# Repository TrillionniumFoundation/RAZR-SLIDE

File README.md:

# RAZR SLIDE

<!-- current-product:start -->
## Current product integration — 2026-10-23

[Current design](CURRENT_DESIGN.md) · [Machine-readable product state](design/current_product.json) · [Implementation and evidence](engineering/product-integration-20261018/README.md)

Exact functional source 042b7689 passed all 1558 actual tests in 36 locked suites, EP4/EP5 native execution and independent readers, and 36442 complete pair domains across three fixed poses. EP4 retains 55 geometric rejections. A separate accessory diagnostic cleared all 1099 continuous pair domains. Full motion remains open: KEY has preserved partial positive evidence; SLIDE native v2 was stopped by the original shared-memory guard after five factory-law probes with no recoverable completed pair rows; SEATING could not start within its original resource gates. Full original L2 K operators were faithfully rebuilt; panel response reached all 3885 columns but failed the original five-probe residual guard, and the new diagnostic could not start within its resource budget. Hosted jobs have no steps or runners. Real inputs, full motion, tolerances, structural qualification and G3-G5 hardware evidence remain unresolved.

The active milestone is a common assembly with flat OLED storage, complete terminations, A/B cell reservations and an operable manual cycle. Measured parts, source specifications and project assumptions retain separate identities.

Configured unit validation: **1564 tests / 36 suites** in `tools/test_suites.json`. Completed execution reports retain their exact commit and scope in `design/current_product.json`; a configured count is not an execution result.

Functional source 042b768903cccbd7a0995317c8598401e0318e2a: 1558 actual tests / 36 suites passed, zero failures/errors/skips, 43 locked packages and required source bytes unchanged. EP4: 15886 pair rows and 55 retained geometry rejections. EP5: 154/154/161 bodies, 36442 finite pair rows, 123 outer-union containments, independent STEP/endpoint readers passed. Three declared fixed-pose control domains: 36442 unique pairs, zero evaluation errors or collision witnesses. Original ten native jobs / 37 commands retain their e76 identity. Follow-on diagnostics record actual passes, numerical rejection, interrupted trials and refused startups separately. Hosted run 39917795794: 18 failed and one skipped job, zero steps/runners/artifacts, current cause unknown. No whole-product or physical/manufacturing acceptance follows.

Accepted numerical evidence: [PR34 installation/service](engineering/installation-control-20261018/DELIVERY_VERIFICATION.json). Bearing research and the older spring experiment retain their own versioned results in the current product state; historical failures remain preserved.
That FE evidence belongs to the original installation geometry. The newly modified product shells have not been structurally requalified.
<!-- current-product:end -->

Private engineering research repository. **`candidate_go=false`; `manufacturing_go=false`.**

## Product constraints

Equal finished A/B dimensions; one approximately 7-inch flexible OLED; no independent rear display; B travels upward 79.75 mm, then seats normally by 8.20 mm; A has priority for the larger battery. 4700 mAh is the unverified TOTAL SYSTEM target; individual A/B cells and capacities are unselected.

## Historical repair baseline

**R50_20261011 is the integration and rejection-validation base**, original archive SHA256 `86f226f9bce3a3f0659737327c7cc32415eed3b9be3f96f35a746ac32844dfd6`. Its seven routes remain rejected. Selection follows whole-inventory review rather than revision numbering or isolated zero-collision results.

R44_FPC_20261013 is a separate, unterminated rear-loop research input. R79 is a separate conditional scalar mathematics branch. Neither establishes an assembled continuous electrical path.

Read the branch comparisons and current review in `engineering/`; do not interchange same-numbered packages from different dates/hashes.

The current R50 guard continuation is [`engineering/r50-topology-repair-20261013`](engineering/r50-topology-repair-20261013). It rejects loose or repeated Wire content hidden in apparently valid single-solid Compounds. All 42 runner tests pass, with two freshly rebuilt 108-cell poses still retaining their B collisions. Earlier repair code and receipts remain as preserved history.

The 121-pose R44 side audit now uses strict participant and signed-common checks in [`engineering/strict-motion-audit-20261013`](engineering/strict-motion-audit-20261013). AABB shortcuts require validated complete participants and a positive axis gap. Its retained shallow-overlap counterexample demonstrates that a checked zero OCC result does not establish positive clearance or continuous-motion qualification. Existing exact distance measurements remain explicitly referenced prior evidence.

## Original records

- `archive/`: reversible exact-byte originals, identities, independent verification, package lineage, historical failures and restoration tool.
- `docs/records/`: 157 directly readable historical Markdown documents.
- `docs/razr-slide-library-inventory.json`: project records and historical visual candidates.
- `baselines/`: frozen, selected source/evidence views. Nested original archives are restored from `archive/` when a historical reproduction script needs them.
- `engineering/`: new independent CAD, BM28 static termination, separated interfaces and mechanical/power safety reviews.

```sh
python3 archive/restore.py --verify
python3 archive/restore.py --restore RAZR_SLIDE_R50_verified_negative_gate_20261011.zip --destination recovered
```

728 originals (3,552,594,718 bytes) are preserved, including superseded visual concepts and two mismatching historical SHA sidecars. Historical images are illustrative records, not current geometry or qualifications.

Raw vendor CAD remains on its authorized source machine where the supplied Readme restricts redistribution. Its provenance, unchanged hashes, exact dimensions and our original reservation-envelope results are recorded; those models are not included here.

## Engineering limits

CAD and software checks can reject a proposal but do not supply actual FPC stackup/fatigue, OEM keep-out permission, physical BM28 connector/PCB/clamp fit and retention qualification, continuous USB SI, battery/BMS short/backfeed/isolation tests, mechanical load/jam/retraction tests, or OLED qualification. STEP exports labelled GHOST are research-only.

Historical R6 design repairs and production blockers are recorded in [`engineering/PRODUCTION_BLOCKERS_R6.md`](engineering/PRODUCTION_BLOCKERS_R6.md). R3/R4 status files remain historical. The [`second-round status`](engineering/qualification-readiness-20261013-r2/CURRENT_STATUS.md) and earlier [`PRODUCTION_STATUS.md`](engineering/manufacturing-closure-20261013/PRODUCTION_STATUS.md) remain historical baselines. Native CAD/ECAD verification and machine receipts are kept with each artifact.

The second round recovers six primary-source documents with variant and OLED conflict records in [`controlled-input-recovery`](engineering/controlled-input-recovery-20261013-r2), and adds an editable hardware return-sensing chain with native terminal verification in [`return-sensing-design`](engineering/return-sensing-design-20261013-r2). It retains conductive PCB bypasses, nonzero healthy parallel return, conditional threshold overlap, zero-load blind spots, and unsafe rearm counterexamples. These are research evidence, not physical qualifications.

R3 adds an [actual pin-keyed endpoint carrier](engineering/endpoint-carrier-repair-20261013-r3), [hardware continuity-permission gates](engineering/electrical-isolation-repair-20261013-r3), and [pinned OEM display/touch/USB identities](engineering/controlled-input-recovery-20261013-r3). Complete phone layout, the physical probe source and matching physical qualifications remain unimplemented or unverified.

No complete controlled phone manufacturing package or matching physical qualification evidence exists in this repository. Its research drawings and software passes do not constitute manufacturing release.

R3 捕获实体修复与独立导出检查：[passive-veto-repair-20261013-r3](engineering/passive-veto-repair-20261013-r3/README.md)。

R4 原厂资料与实改：[OLED来源](engineering/oled-controlled-search-20261013-r4/README.md)、[FPC与RA材料](engineering/fpc-controlled-search-20261013-r4/README.md)、[自主干回路与WDI修复](engineering/proof-detector-design-20261013-r4/README.md)。厂家资料请求以[修正R4请求](engineering/production-inputs-20261013-r4/targeted-controlled-input-request.json)为准：4700mAh是整机目标，A优先大电池。

R4 历史冻结状态：[PRODUCTION_BLOCKERS_R4.md](engineering/PRODUCTION_BLOCKERS_R4.md)。

R4 实际[单切断PCB与原生生产格式导出](engineering/pcb-source-repair-20261013-r4/README.md)、[盖紧固与撤钥干涉修复](engineering/mechanical-return-design-20261013-r4/README.md)。两者均是未获实物放行的研究台架。

R5/R6 历史实改与证据：[G2 路线与全部拒绝实体](engineering/fpc-g2-route-candidates-20261013-r6/README.md)、[完整材料运动](engineering/fpc-material-motion-20261013-r5/README.md)、[无损 NPZ 恢复](engineering/fpc-material-motion-transport-20261013-r5/README.md)、[初版 OLED 模组规格](engineering/oled-orderable-module-search-20261013-r5/README.md)、[原厂条件叠层](engineering/fpc-layer-stackup-20261013-r5/README.md)、[四相电气自检](engineering/proof-selftest-design-20261013-r5/README.md)、[A 链四块研究 PCB 与实际原生导出](engineering/power-chain-pcba-20261013-r5/README.md)。

单正实体、零 DRC/ERC 和研究 STEP 不等于完整手机可生产。指定 OLED/FPC、真实整机装配、完整 PCB 及机械/双电池/USB/OLED 实物资格仍按 [R6 历史门槛](engineering/PRODUCTION_BLOCKERS_R6.md)约束。`manufacturing_go=false`。

R6 [实际取得的 39 页 OLED 候选原始规格与来源核验](engineering/controlled-inputs-web-20261013-r6/README.md)保留完整40pin事实和动态资格缺口，未替代指定受控OLED。

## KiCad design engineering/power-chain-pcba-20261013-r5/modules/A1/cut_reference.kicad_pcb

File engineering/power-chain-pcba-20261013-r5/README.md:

# Four-board A power-chain research PCBA, R5

**仅 A 电池电源链的四块研究板；A1/A2 是两个源端切口，B1/B2 是 A 链的两个接收切口。没有独立 B 电池电路、双电池充电合流或 USB 电路。`manufacturing_go=false`。** These are unpowered bench reference boards, not the complete phone PCB or a released assembly.

The actual series chain is `A_PACK_P -> A1 -> A_MID_P -> A2 -> A_TX_P -> harness -> A_RX_P -> B1 -> A_RX_MID_P -> B2 -> SYS_B_P`. The main return is routed through pin 2 of each J1/J2 connector and the matching harness return conductors. Raw CELL_P/CELL_N never enter these boards. The protected pack and bench load are explicit external boundaries; no pack protector, cell selection, phone regulator, SoC/storage/RF/audio/camera/OLED circuitry is implemented here.

## Actual hardware source

Each 45 × 24 × 1.6-mm board has 17 annotated items, 42 unique pins, 46 copper pads, 68 routed segments and **13 vias**. It contains a TPS259470LRPW latch-off eFuse, a VOS618A-8X001T optical active-high enable, four specified Panasonic resistors, three TDK 1-uF capacitors (one input, two parallel output), a KEMET 10-nF C0G slew capacitor, an input SMBJ5.0CA-E3/52 bidirectional TVS and an output PMEG3050EP Schottky clamp. There are three JST PH static headers plus two isolated-instrument-only observation pads. Selected bench part codes and source URLs/hashes are in `primary_component_sources.json` and the per-board BOM files. They are not selected or qualified phone BOM parts.

The optical LED input/reference has no copper connection to the power return. Each stage has its own LED pair and series resistor. The phototransistor collector connects to that stage's local protected VIN, emitter to EN, and a local 47-kohm resistor defaults EN low. The independent reader checks all actual copper pad/track/via geometry: the conservative nominal XY distance between each optical input domain and its power domain is **5.000 mm**. This is not a tolerance, creepage, dielectric, isolation-fault or contamination qualification. The manufacturer's 3750-Vrms optocoupler test is not a board certificate. A shared controller or common wiring failure can still affect multiple stages; independent net names alone do not establish independent fault domains.

Bench inputs are limited by the design assumption to **3.4–4.4 V, <=1 A load, 25 C**. A 2.21-kohm ILM resistor gives about 1.509 A nominal current limit by the TI equation; actual current, drop and thermal rise are unmeasured. `opto_bound_receipt.json` reports a 94.66-uA maximum calculated collector load, 9.494-mV conditional dark EN level and 2.3-V conditional enabled level. It preserves the exact datasheet test conditions: CTR is at 1 mA/5 V/25 C; saturation and dark-current bounds also have specified conditions. Using the saturation bound with stronger LED current and smaller collector load, and using the diode's 50-mA VF bound at lower current, are explicit monotonicity inferences. Full-temperature and dynamic cutoff bounds remain unavailable. No conditional calculation is a physical qualification.

PMEG3050EP's 5-A rating depends on mounting/duty/temperature. Negative spikes above the 1-A data point can exceed TPS25947's continuous -0.3-V OUT limit; waveform qualification remains open. TVS energy, capacitor effective value/DC bias, cable inductance, source fault current, finite OFF leakage, quiet-ground/thermal layout, copper current rating and fault energy are not qualified. Neither TVS nor Schottky placement proves transient survival.

`harness_terminal_schedule.csv` defines **18 conductors / 36 conductor ends** with explicit positive/return and four isolated-control pairs. It specifies JST PHR-2 housings and SPH-002T-P0.5S contacts with Alpha Wire 3050 AWG24, and gives bench cut lengths. Alpha's published OD envelope fits the selected contact's nominal range, and its 10-diameter bend radius is retained. This is a static lab harness schedule, not the project's qualified moving FPC or a physically assembled/crimp-tested harness. Wire packaging suffixes, fixture-side terminations and routing/strain relief are not frozen for production.

## Native evidence and retained failures

- Main/qian-qi, KiCad 7.0.11: four fresh serialized-board DRC processes report **0 violations / 0 unconnected / 0 footprint errors**, under unchanged 0.1-mm copper and 0.25-mm hole rules. No exclusions or severity changes were added.
- Pocket4, KiCad 9.0.8: four final XML and four final ERC commands exit 0; ERC has no violations at any severity. An independent reader matches **168 unique PCB/schematic pins**, exact eFuse/opto/Schottky pin functions and final frozen schematic/symbol hashes. An initial stage naming pass prefixed three vendor pin names; their numeric maps were correct, and the names were corrected with a separate retained source archive and fresh native XML/ERC/SVG run. PCB copper did not change.
- Main: 24 actual native manufacturing-format export commands exit 0. The files include **28 Gerber layers**, four PTH/NPTH drill sets and maps, **48 SMD placement rows**, native PCB/schematic SVGs and four **BOARD_ONLY** STEP files. The validated PCB bytes remain unchanged. The original schematic SVGs under `native_main` are historical; final corrected schematic drawings are under `native_pocket_v2`.
- Independent STEP import checks all roots: four valid positive board solids, each 45 × 24 × 1.6 mm, matching eight 0.75-mm pad holes. Native KiCad7 STEP does not include the **13 via bores**, any component models, housings/wires, chassis or assembly. SMD placement excludes the three PTH headers and two observation pads; it is not a full assembly or manual PTH placement instruction.
- Three actual copper negative variants remain: missing ILM connection gives one dangling warning and one unconnected error; a VIN/OUT bridge gives two DRC violations; an optical C/E bridge gives three. These are detected CAD faults, not energized hardware fault tests.
- `chain_fault_paths.json` retains live paths when both A cuts weld, when both B receiving cuts weld, and when cross-board protected-input/harness or system-bus/harness bridges occur. The three legacy raw-A/raw-B/system-bus bridge cases remain **not physically excluded**. Sixteen ideal normal combinations are enumerated separately; finite leakage, parallel return and real fault energy are not modeled as safe.

The first independent verifier's expected via count was wrong and is retained under `rejected-initial-verifier-count`. R4's earlier narrative said seven omitted vias; an actual source count is **nine** (two VIN plus seven ground), while R5 has thirteen. The R4 source and evidence were preserved unchanged; the board STEP's eight pad-hole geometry remains correct.

The OLED review agent independently read all four BOM/XML/CPL/PCB sets without invoking the builder or changing files: all 17 BOM entries, 12 SMD placements and 42 unique pins per board matched. Native copper and final schematic previews were visually inspected. Inkscape exited 0 with its known GtkRecentManager startup warning.

No hardware was powered, no sample was manufactured, and no supplier message, NDA or order was submitted. True assembly, B battery/charging/USB/OLED circuits, controlled moving FPC data and all physical product qualifications remain open. Equal cabin sizes, one approximately 7-inch OLED, 79.75-mm upward stroke, 8.2-mm seating, A battery priority and the **4700-mAh total system target** remain unchanged.

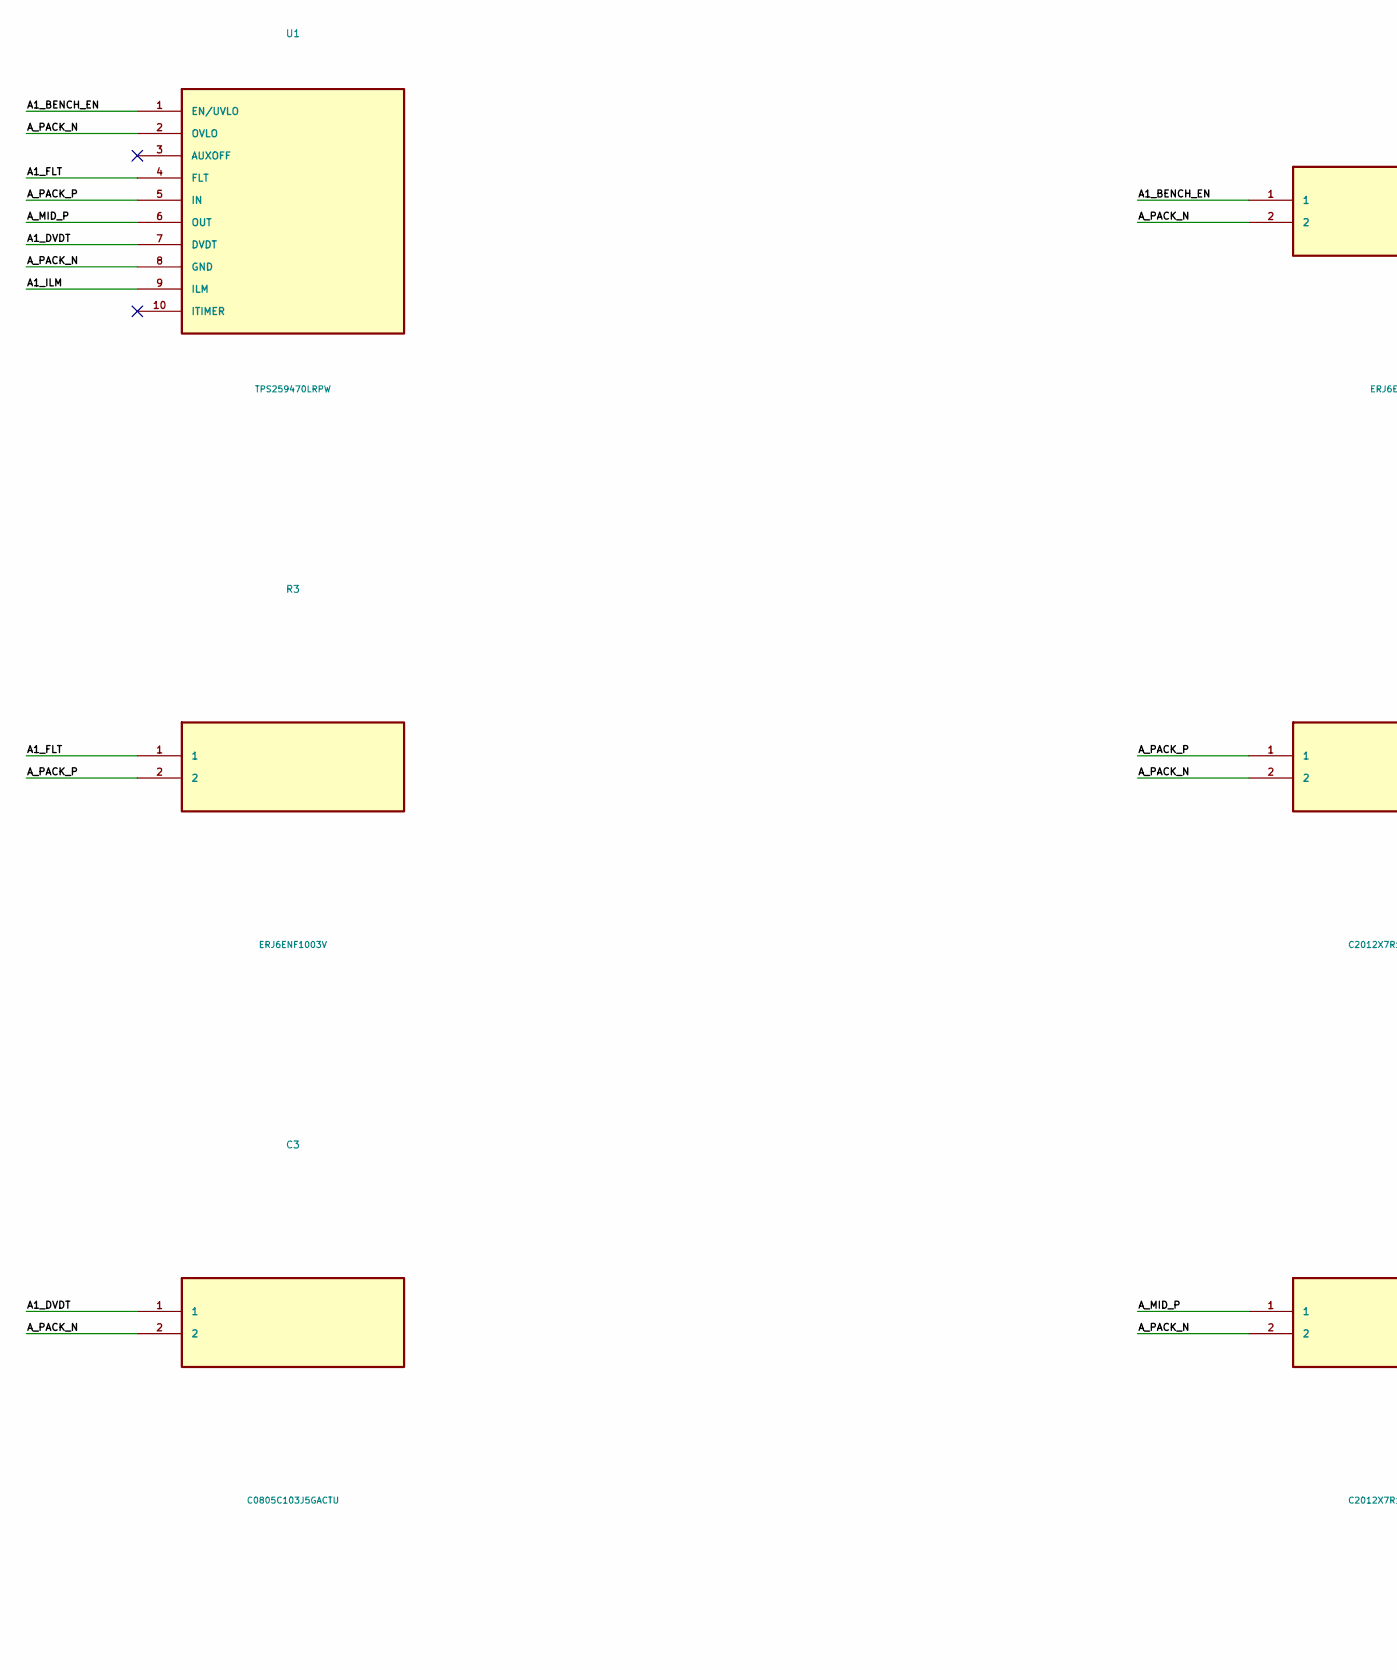
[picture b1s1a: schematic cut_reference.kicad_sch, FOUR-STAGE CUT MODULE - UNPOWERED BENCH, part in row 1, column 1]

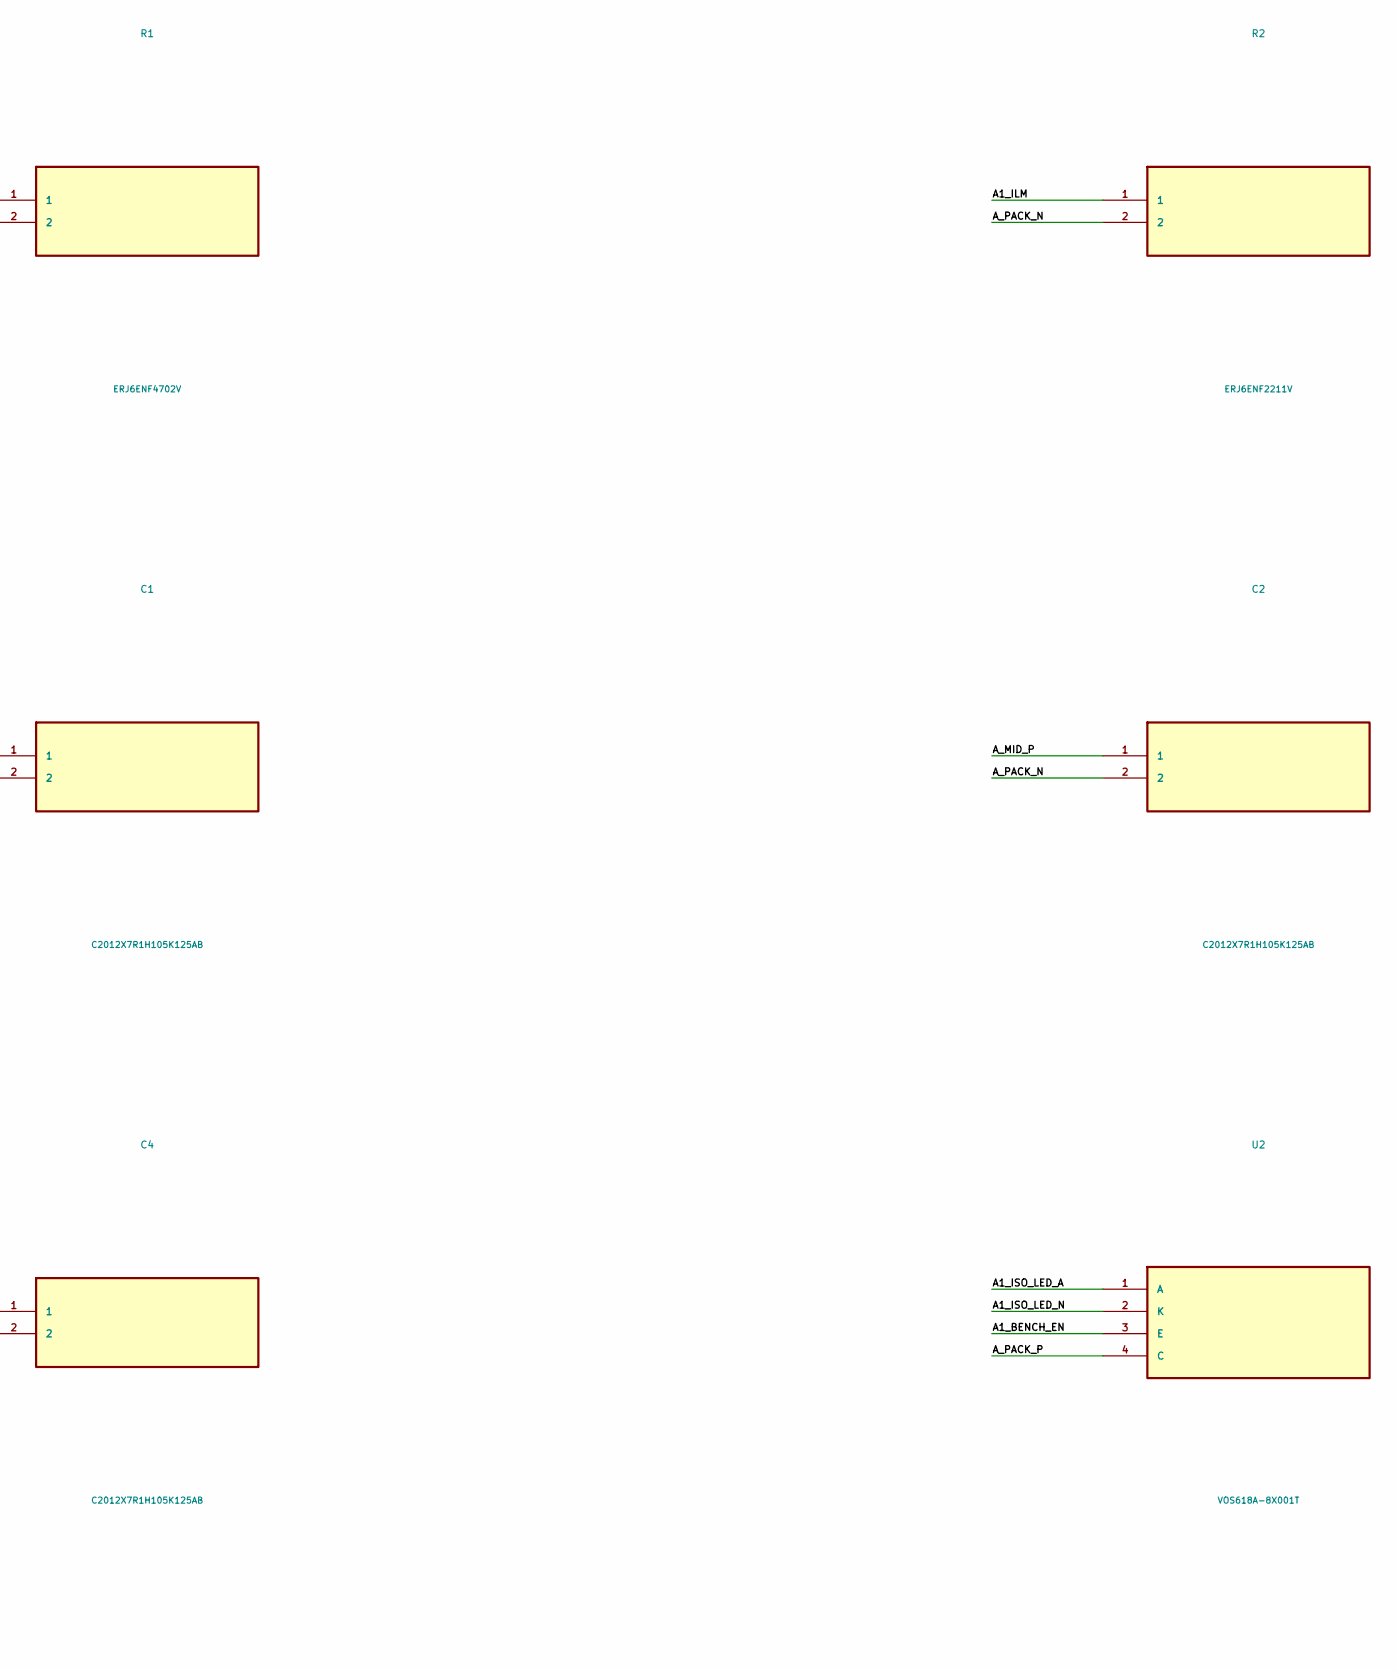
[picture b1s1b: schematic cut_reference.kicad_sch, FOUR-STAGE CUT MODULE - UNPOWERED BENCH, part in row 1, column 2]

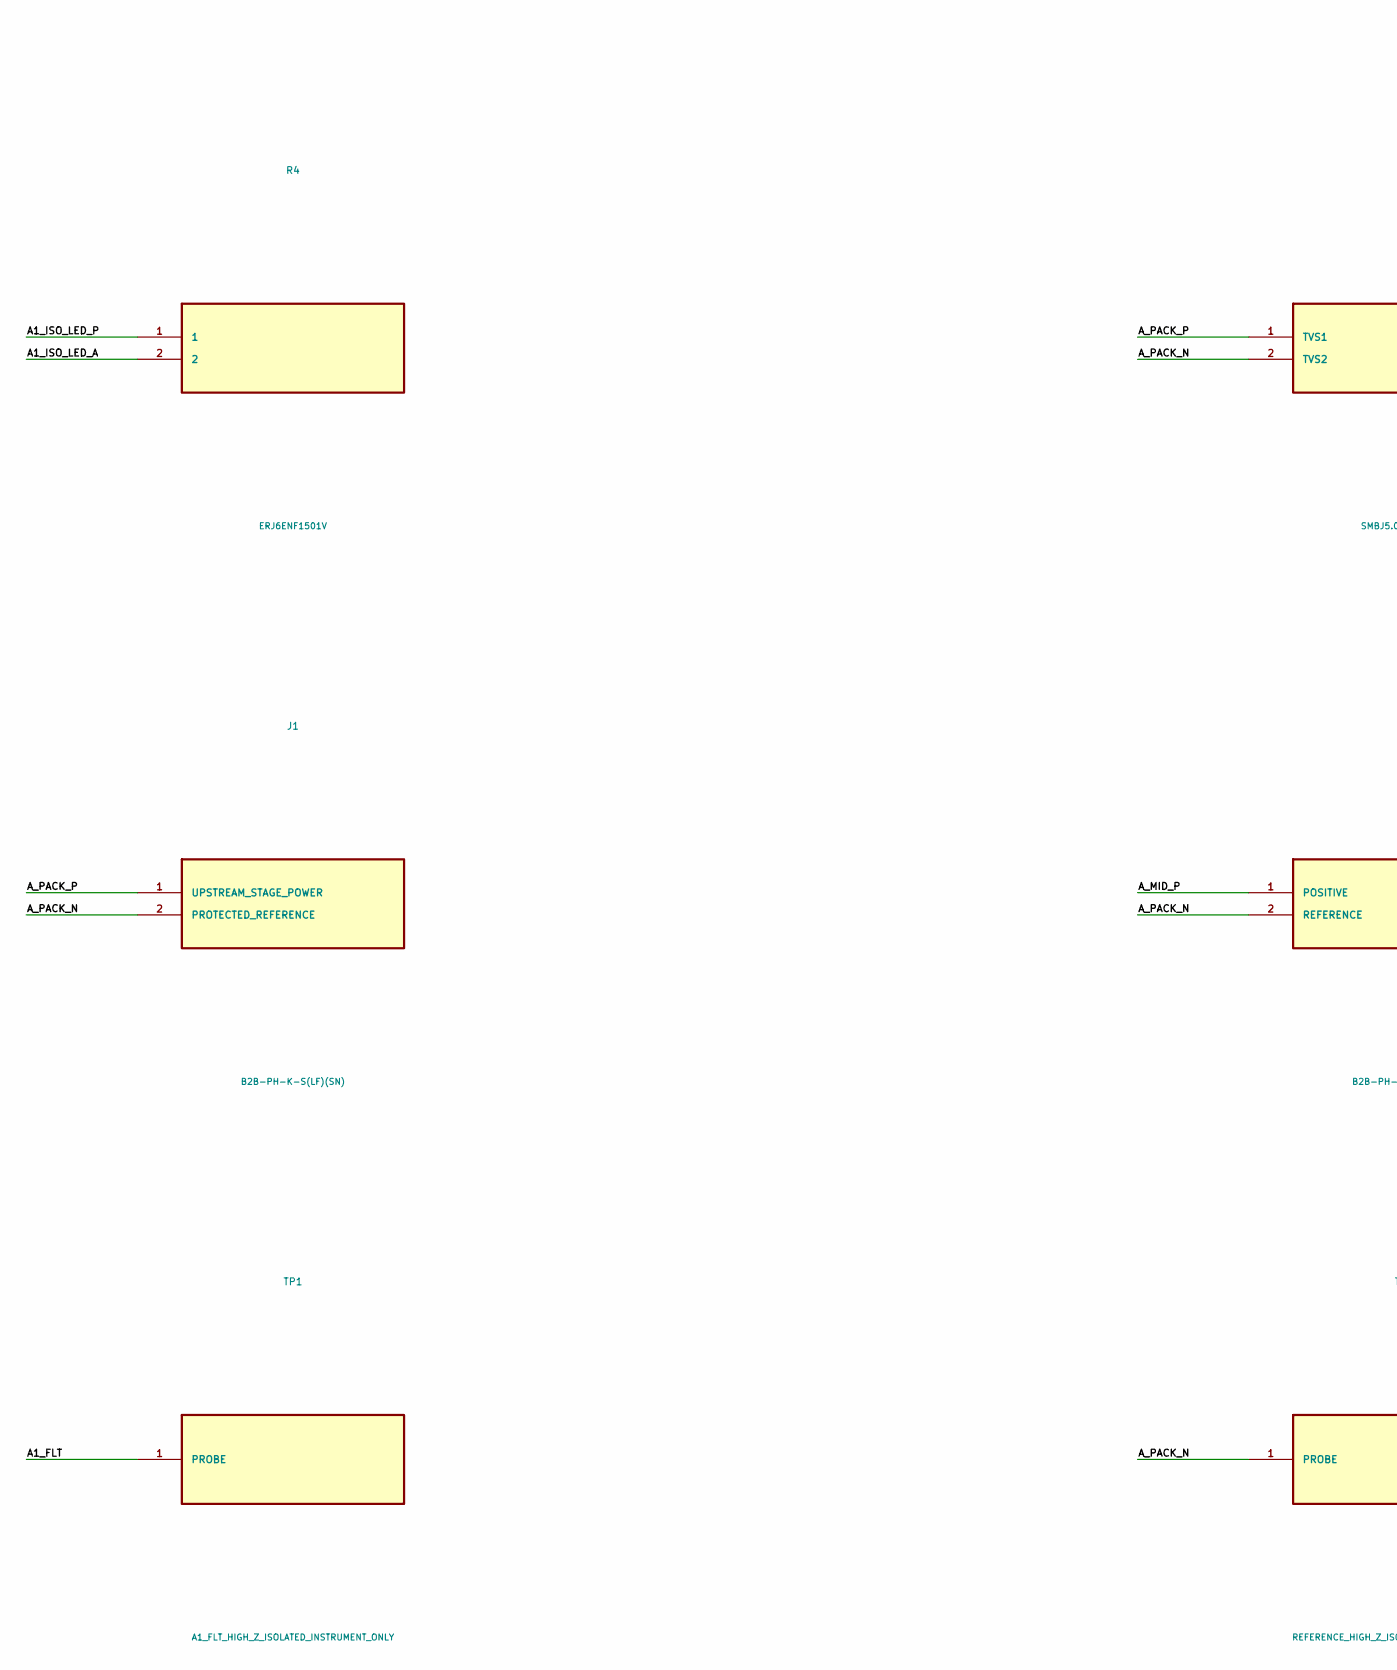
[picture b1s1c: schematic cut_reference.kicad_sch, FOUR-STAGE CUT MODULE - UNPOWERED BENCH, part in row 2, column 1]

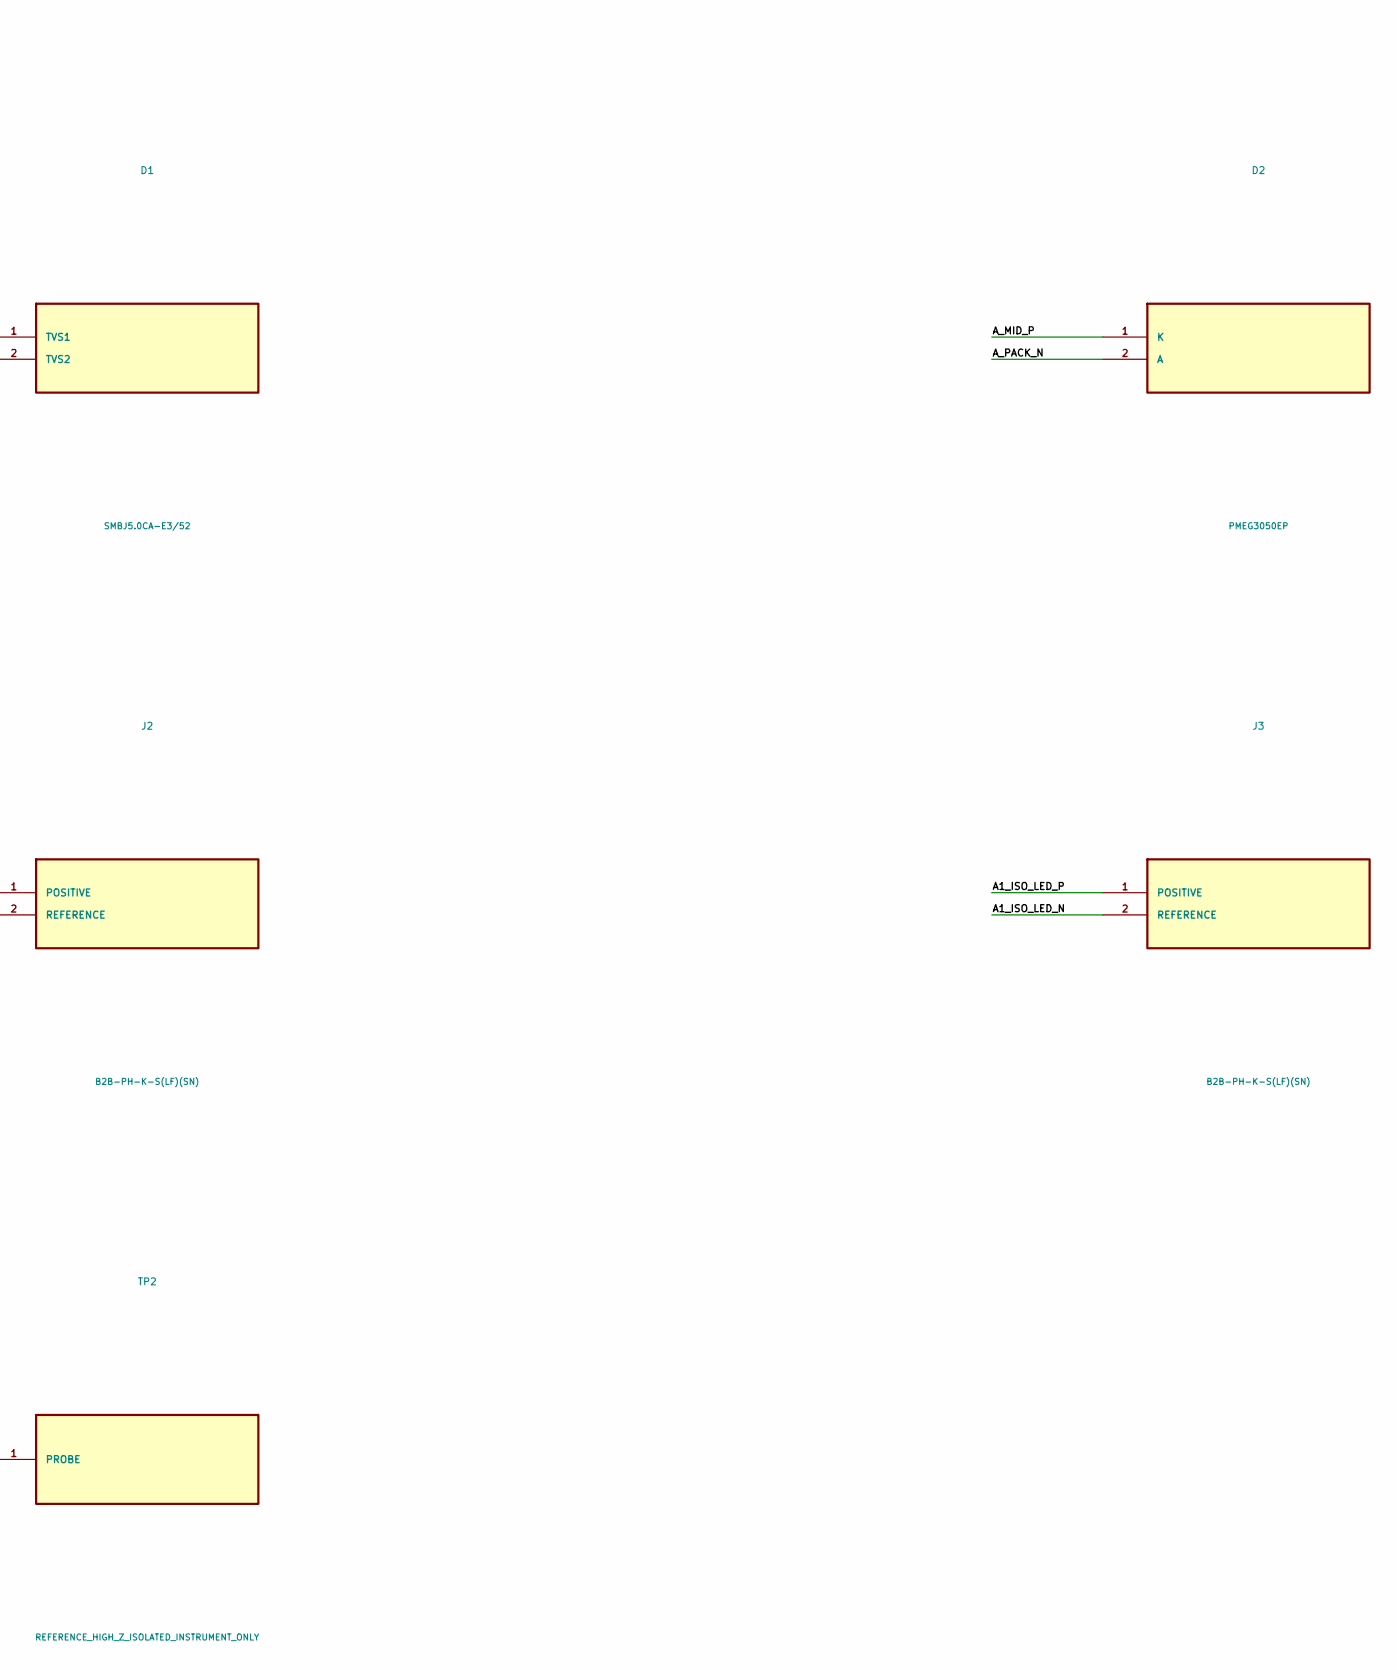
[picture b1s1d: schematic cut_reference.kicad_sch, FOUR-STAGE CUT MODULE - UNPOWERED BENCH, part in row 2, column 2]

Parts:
C1, C2, C4: C2012X7R1H105K125AB; Passive_0805_BENCH
C3: C0805C103J5GACTU; Passive_0805_BENCH
D1: SMBJ5.0CA-E3/52; SMB_OWNED_NOMINAL
D2: PMEG3050EP; SOD128_OWNED_NOMINAL
J1: B2B-PH-K-S(LF)(SN); PH2_OWNED_VERTICAL_IN
J2: B2B-PH-K-S(LF)(SN); PH2_OWNED_VERTICAL_OUT
J3: B2B-PH-K-S(LF)(SN); PH2_OWNED_HORIZONTAL
R1: ERJ6ENF4702V; Passive_0805_Vertical_BENCH
R2: ERJ6ENF2211V; Passive_0805_BENCH
R3: ERJ6ENF1003V; Passive_0805_BENCH
R4: ERJ6ENF1501V; Passive_0805_BENCH
TP1: A1_FLT_HIGH_Z_ISOLATED_INSTRUMENT_ONLY; Probe_1p8mm
TP2: REFERENCE_HIGH_Z_ISOLATED_INSTRUMENT_ONLY; Probe_1p8mm
U1: TPS259470LRPW; RPW0010A_OWNED_NOMINAL
U2: VOS618A-8X001T; VOS618A_OWNED_DATASHEET

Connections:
A1_BENCH_EN: R1.1, U1.1 (EN/UVLO), U2.3 (E)
A1_DVDT: C3.1, U1.7 (DVDT)
A1_FLT: R3.1, TP1.1, U1.4 (FLT)
A1_ILM: R2.1, U1.9 (ILM)
A1_ISO_LED_A: R4.2, U2.1 (A)
A1_ISO_LED_N: J3.2 (REFERENCE), U2.2 (K)
A1_ISO_LED_P: J3.1 (POSITIVE), R4.1
A_MID_P: C2.1, C4.1, D2.1 (K), J2.1 (POSITIVE), U1.6 (OUT)
A_PACK_N: C1.2, C2.2, C3.2, C4.2, D1.2 (TVS2), D2.2 (A), J1.2 (PROTECTED_REFERENCE), J2.2 (REFERENCE), R1.2, R2.2, TP2.1, U1.2 (OVLO), U1.8 (GND)
A_PACK_P: C1.1, D1.1 (TVS1), J1.1 (UPSTREAM_STAGE_POWER), R3.2, U1.5 (IN), U2.4 (C)

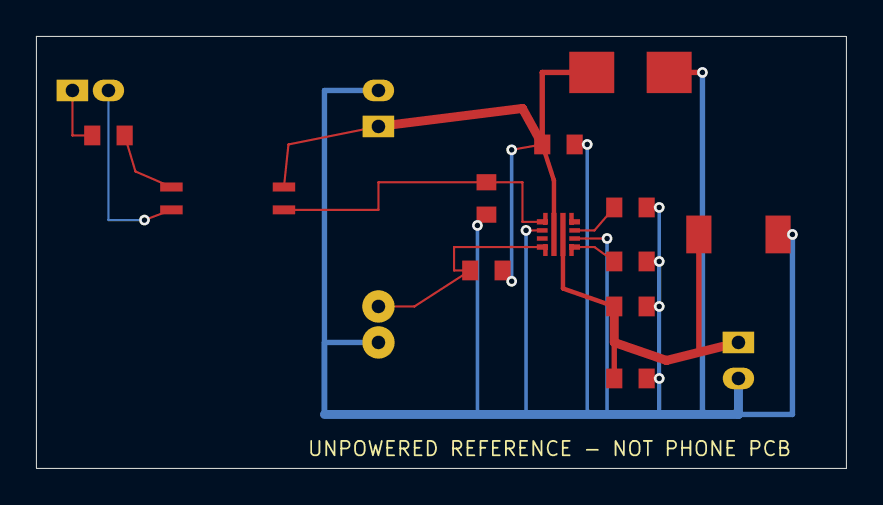
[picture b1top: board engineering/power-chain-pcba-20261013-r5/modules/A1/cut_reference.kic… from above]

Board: 2 copper layers, 45.0 x 24.0 mm, 17 parts (0 on the bottom side), 10 nets.
